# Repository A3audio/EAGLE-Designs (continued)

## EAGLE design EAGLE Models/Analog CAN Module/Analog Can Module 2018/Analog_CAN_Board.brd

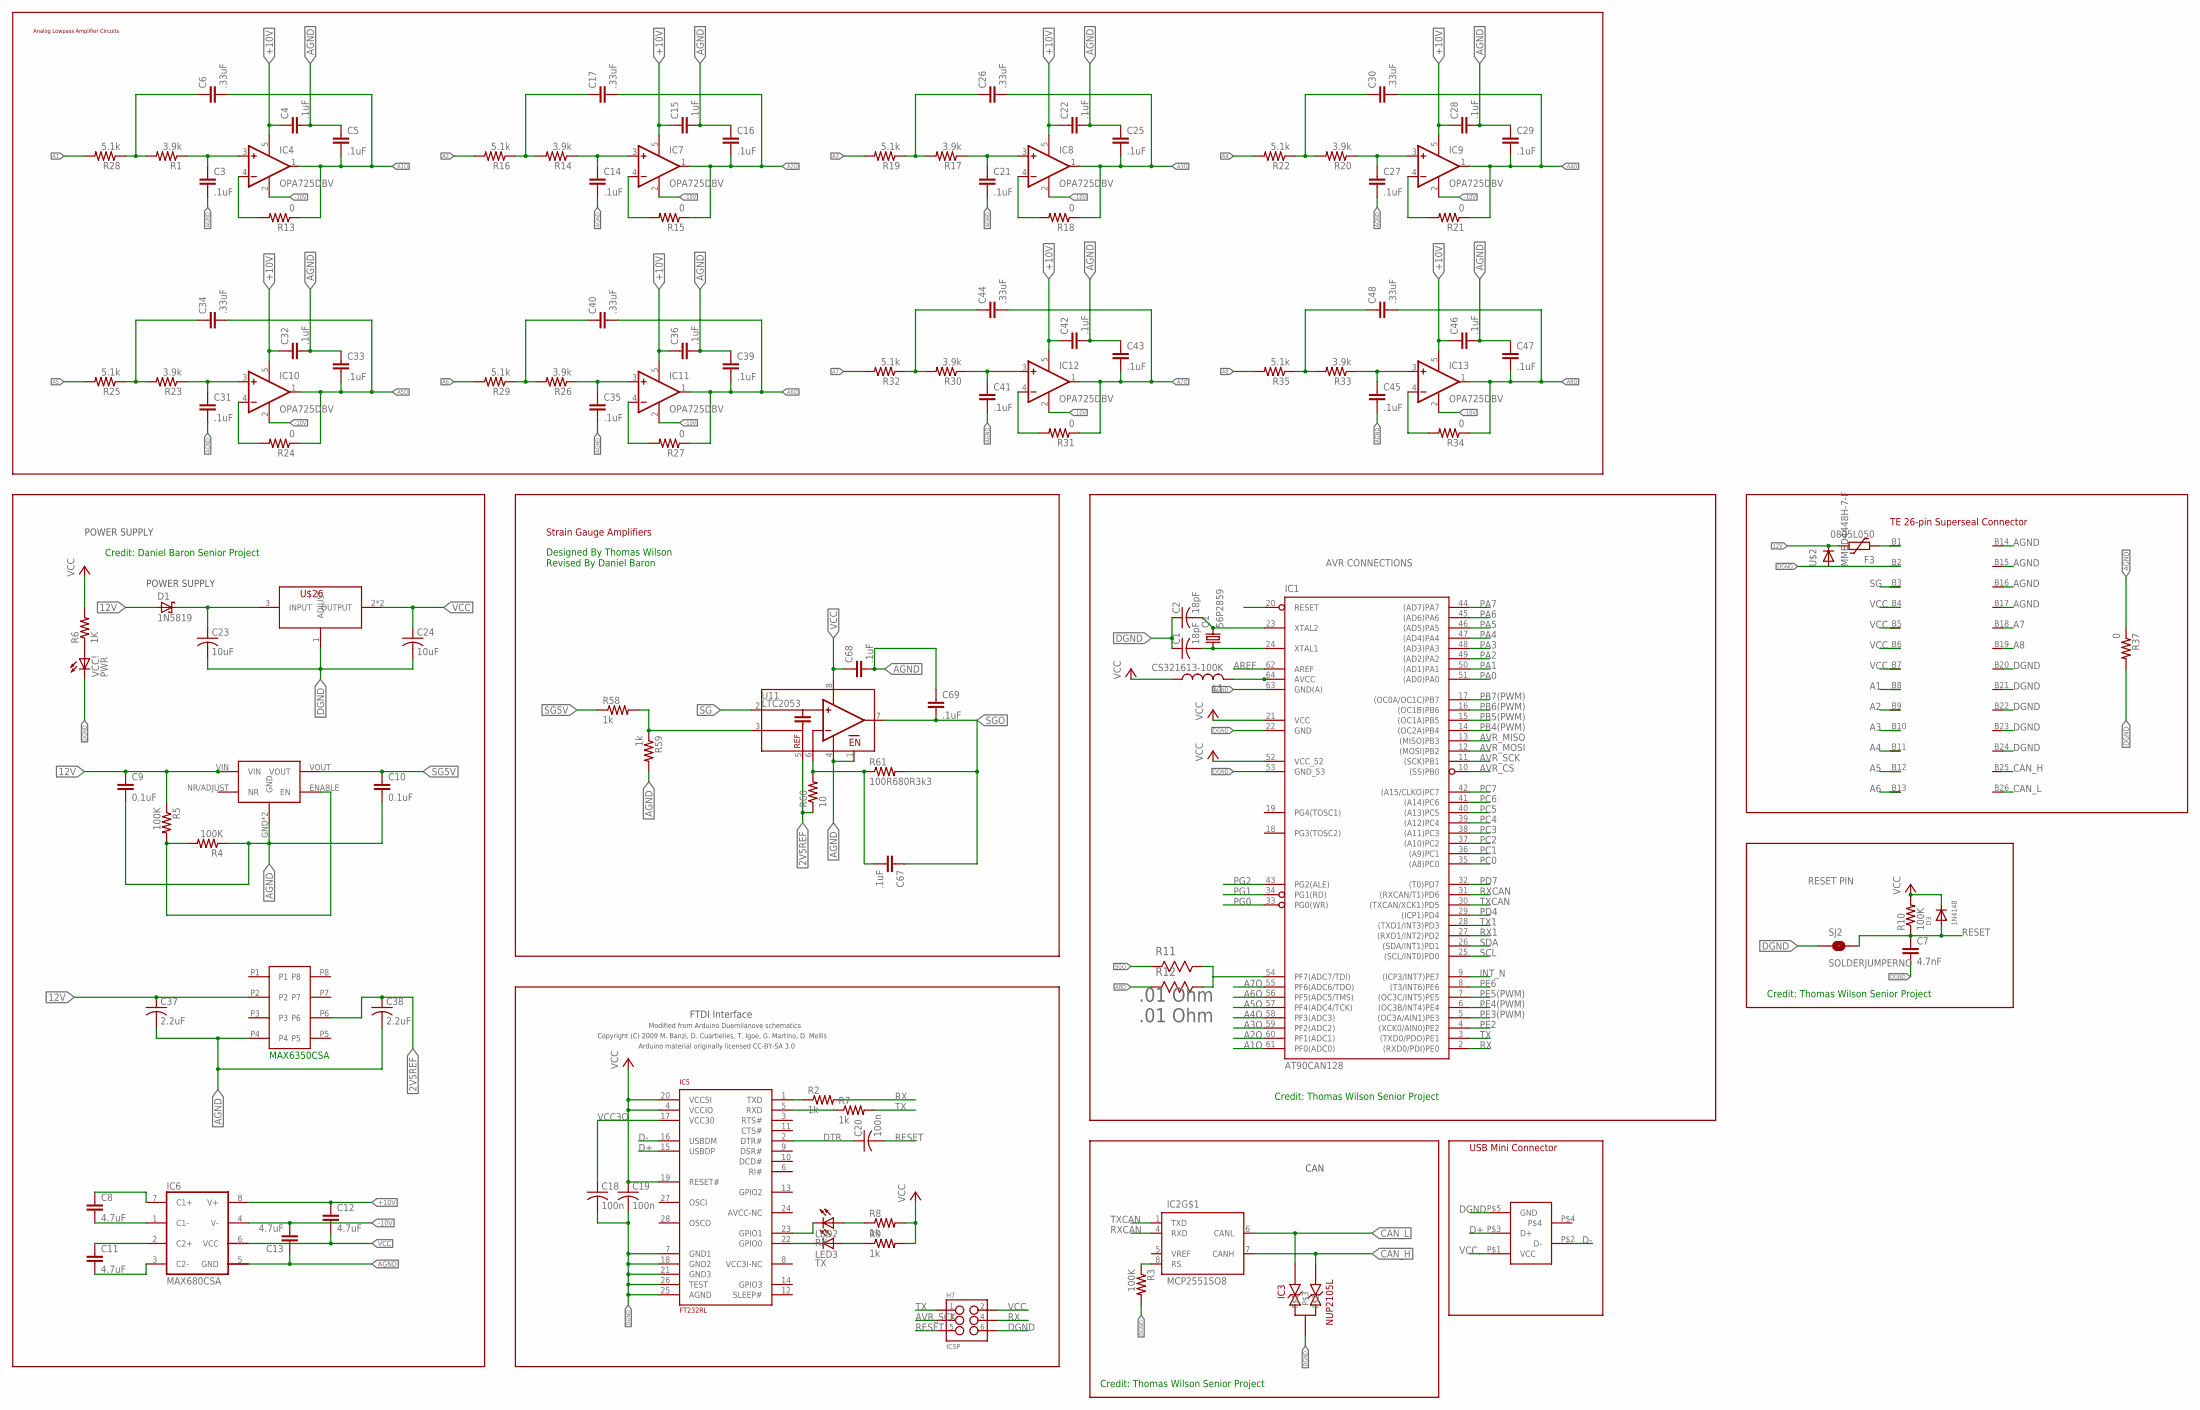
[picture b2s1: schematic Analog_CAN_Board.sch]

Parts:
C1, C2: 18pF; C0805
C3, C4, C5, C14, C15, C16, C21, C22, C25, C27, C28, C29, C31, C32, C33, C35, C36, C39, C41, C42, C43, C45, C46, C47, C67, C68, C69: .1uF; 0603-CAP
C6, C17, C26, C30, C34, C40, C44, C48: .33uF; 0603-CAP
C7: 4.7nF; 0603-CAP
C8, C11, C12, C13: 4.7uF; 0603-CAP
C9, C10: 0.1uF; C0603
C18, C19, C20: 100n; C0805
C23, C24: 10uF; C0603
C37, C38: 2.2uF; C0603
D1: 1N5819; DO41-7.6
D3: 1N4148; SOD-123
F3: 0805L050; 0805L
H7: ICSP; 2X3_SMD_FCI_54202-G30
IC1: AT90CAN128; TQFP64
IC2: MCP2551SO8; SO08
IC3: NUP2105L; SOT-23
IC4, IC7, IC8, IC9, IC10, IC11, IC12, IC13: OPA725DBV; SOT23-5
IC5: FT232RL; SSOP28
IC6: MAX680CSA; SO08
L1: CS321613-100K; L3216C
LED2: RX; CHIPLED_0805
LED3: TX; CHIPLED_0805
Q1: 56P2859; HC49UP
R1, R14, R17, R20, R23, R26, R30, R33: 3.9k; 0603-RES
R2, R7, R8, R9: 1k; R0805
R3, R10: 100K; R0805
R4, R5: 100K; M0805
R6: 1K; R0805
R11, R12: .01 Ohm; RESC1608X60N
R13, R15, R18, R21, R24, R27, R31, R34, R37: 0; 0603-RES
R16, R19, R22, R25, R28, R29, R32, R35: 5.1k; 0603-RES
R58, R59: 1k; 0603-RES
R60: 10; 0603-RES
R61: 100R680R3k3; 0603-RES
SJ2: SOLDERJUMPERNO; SJ_2S-NO
U11: LTC2053; MSOP8
U$1: 1734753-1_MINIUSB_CON
U$2: MMBD4448H-7-F; SOT23-3
U$3: SUPERSEAL1.0_26POS
U$5: REG-104GA-5; REG104GA-5
U$10V2V5: MAX6350CSA; 8-SOIC
U$26: NCP1117; SOT-223-4
VCC!: PWR; CHIPLED_0805

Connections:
2V5REF: C38.1, R60.1, U11.5 (REF), U$10V2V5.P6
5V_REG_IN: C23.1, D1.C, U$26.3 (INPUT)
12V: C9.1, C37.1, D1.A, F3.1, R5.1, U$2.3 (C), U$5.VIN, U$10V2V5.P2
+10V: C4.1, C12.1, C15.1, C22.1, C28.1, C32.1, C36.1, C42.1, C46.1, IC4.5 (V+), IC6.8 (V+), IC7.5 (V+), IC8.5 (V+), IC9.5 (V+), IC10.5 (V+), IC11.5 (V+), IC12.5 (V+), IC13.5 (V+)
-10V: C13.2, IC4.2 (V-), IC6.4 (V-), IC7.2 (V-), IC8.2 (V-), IC9.2 (V-), IC10.2 (V-), IC11.2 (V-), IC12.2 (V-), IC13.2 (V-)
A1: R28.2, U$3.B8
A1O: C5.2, C6.2, IC1.61 (PF0(ADC0)), IC4.1 (OUT), R13.1
A2: R16.2, U$3.B9
A2O: C16.2, C17.2, IC1.60 (PF1(ADC1)), IC7.1 (OUT), R15.1
A3: R19.2, U$3.B10
A3O: C25.2, C26.2, IC1.59 (PF2(ADC2)), IC8.1 (OUT), R18.1
A4: R22.2, U$3.B11
A4O: C29.2, C30.2, IC1.58 (PF3(ADC3)), IC9.1 (OUT), R21.1
A5: R25.2, U$3.B12
A5O: C33.2, C34.2, IC1.57 (PF4(ADC4/TCK)), IC10.1 (OUT), R24.1
A6: R29.2, U$3.B13
A6O: C39.2, C40.2, IC1.56 (PF5(ADC5/TMS)), IC11.1 (OUT), R27.1
A7: R32.2, U$3.B18
A7O: C43.2, C44.2, IC1.55 (PF6(ADC6/TDO)), IC12.1 (OUT), R31.1
A8: R35.2, U$3.B19
A8O: C47.2, C48.2, IC13.1 (OUT), R12.2, R34.1
AGND: C3.2, C4.2, C5.1, C9.2, C10.2, C13.1, C14.2, C15.2, C16.1, C21.2, C22.2, C25.1, C27.2, C28.2, C29.1, C31.2, C32.2, C33.1, C35.2, C36.2, C37.2, C38.2, C39.1, C41.2, C42.2, C43.1, C45.2, C46.2, C47.1, C68.2, C69.1, IC1.63 (GND(A)), IC2.2 (GND), IC6.5 (GND), R4.1, R37.1, R59.2, U11.1 (EN), U11.4 (V-), U$3.B14, U$3.B15, U$3.B16, U$3.B17, U$5.GND, U$5.HEATGND (GND), U$10V2V5.P4
AREF: IC1.62 (AREF)
AVR_CS: IC1.10 ((SS)PB0)
AVR_MISO: IC1.13 ((MISO)PB3)
AVR_MOSI: IC1.12 ((MOSI)PB2)
AVR_SCK: H7.3, IC1.11 ((SCK)PB1)
CAN_H: IC2.7 (CANH), IC3.2, U$3.B25
CAN_L: IC2.6 (CANL), IC3.1, U$3.B26
D+: IC5.15 (USBDP), U$1.P$3 (D+)
D-: IC5.16 (USBDM), U$1.P$2 (D-)
DGND: C1.1, C2.1, C7.2, C18.2, C19.2, C23.2, C24.2, H7.6, IC1.22 (GND), IC1.53 (GND_53), IC3.3, IC5.7 (GND1), IC5.18 (GND2), IC5.21 (GND3), IC5.25 (AGND), IC5.26 (TEST), R3.2, R37.2, SJ2.1, U$1.P$5 (GND), U$2.1 (A), U$3.B2, U$3.B20, U$3.B21, U$3.B22, U$3.B23, U$3.B24, U$26.1 (ADJUST), VCC!.C
DTR: C20.1, IC5.2 (DTR#)
INT_N: IC1.9 ((ICP3/INT7)PE7)
M8RXD: IC5.1 (TXD), R2.1
M8TXD: IC5.5 (RXD), R7.1
unnamed: F3.2, U$3.B1
unnamed: R4.2, R5.2, U$5.ENABLE (EN)
unnamed: C6.1, R1.2, R28.1
unnamed: IC2.8 (RS), R3.1
unnamed: R6.1, VCC!.A
unnamed: C1.2, IC1.24 (XTAL1), Q1.1
unnamed: C3.1, IC4.3 (+IN), R1.1
unnamed: IC1.54 (PF7(ADC7/TDI)), R11.1, R12.1
unnamed: IC4.4 (-IN), R13.2
unnamed: C8.1, IC6.7 (C1+)
unnamed: C11.1, IC6.2 (C2+)
unnamed: IC1.64 (AVCC), L1.2
unnamed: C8.2, IC6.1 (C1-)
unnamed: C11.2, IC6.3 (C2-)
unnamed: C14.1, IC7.3 (+IN), R14.1
unnamed: IC7.4 (-IN), R15.2
unnamed: C17.1, R14.2, R16.1
unnamed: R58.2, R59.1, U11.3 (+IN)
unnamed: C67.2, R60.2, R61.1, U11.6 (RG)
unnamed: C21.1, IC8.3 (+IN), R17.1
unnamed: IC8.4 (-IN), R18.2
unnamed: IC5.23 (GPIO1), LED2.C
unnamed: C26.1, R17.2, R19.1
unnamed: IC5.22 (GPIO0), LED3.C
unnamed: LED2.A, R8.1
unnamed: LED3.A, R9.1
unnamed: C27.1, IC9.3 (+IN), R20.1
unnamed: IC9.4 (-IN), R21.2
unnamed: C30.1, R20.2, R22.1
unnamed: C31.1, IC10.3 (+IN), R23.1
unnamed: IC10.4 (-IN), R24.2
unnamed: C34.1, R23.2, R25.1
unnamed: C35.1, IC11.3 (+IN), R26.1
unnamed: IC11.4 (-IN), R27.2
unnamed: C40.1, R26.2, R29.1
unnamed: C41.1, IC12.3 (+IN), R30.1
unnamed: IC12.4 (-IN), R31.2
unnamed: C44.1, R30.2, R32.1
unnamed: C45.1, IC13.3 (+IN), R33.1
unnamed: IC13.4 (-IN), R34.2
unnamed: C48.1, R33.2, R35.1
PA0: IC1.51 ((AD0)PA0)
PA1: IC1.50 ((AD1)PA1)
PA2: IC1.49 ((AD2)PA2)
PA3: IC1.48 ((AD3)PA3)
PA4: IC1.47 ((AD4)PA4)
PA5: IC1.46 ((AD5)PA5)
PA6: IC1.45 ((AD6)PA6)
PA7: IC1.44 ((AD7)PA7)
PB4(PWM): IC1.14 ((OC2A)PB4)
PB5(PWM): IC1.15 ((OC1A)PB5)
PB6(PWM): IC1.16 ((OC1B)PB6)
PB7(PWM): IC1.17 ((OC0A/OC1C)PB7)
PC0: IC1.35 ((A8)PC0)
PC1: IC1.36 ((A9)PC1)
PC2: IC1.37 ((A10)PC2)
PC3: IC1.38 ((A11)PC3)
PC4: IC1.39 ((A12)PC4)
PC5: IC1.40 ((A13)PC5)
PC6: IC1.41 ((A14)PC6)
PC7: IC1.42 ((A15/CLKO)PC7)
PD4: IC1.29 ((ICP1)PD4)
PD7: IC1.32 ((T0)PD7)
PE2: IC1.4 ((XCK0/AIN0)PE2)
PE3(PWM): IC1.5 ((OC3A/AIN1)PE3)
PE4(PWM): IC1.6 ((OC3B/INT4)PE4)
PE5(PWM): IC1.7 ((OC3C/INT5)PE5)
PE6: IC1.8 ((T3/INT6)PE6)
PG0: IC1.33 (PG0(WR))
PG1: IC1.34 (PG1(RD))
PG2: IC1.43 (PG2(ALE))
RESET: C7.1, C20.2, D3.A, H7.5, IC1.20 (RESET), R10.1, SJ2.2
RX: H7.4, IC1.2 ((RXD0/PDI)PE0), R2.2
RX1: IC1.27 ((RXD1/INT2)PD2)
RXCAN: IC1.31 ((RXCAN/T1)PD6), IC2.4 (RXD)
SCL: IC1.25 ((SCL/INT0)PD0)
SDA: IC1.26 ((SDA/INT1)PD1)
SG: U11.2 (-IN), U$3.B3
SG5V: C10.1, R58.1, U$5.VOUT
SGO: C67.1, C69.2, R11.2, R61.2, U11.7 (OUT)
TX: H7.1, IC1.3 ((TXD0/PDO)PE1), R7.2
TX1: IC1.28 ((TXD1/INT3)PD3)
TXCAN: IC1.30 ((TXCAN/XCK1)PD5), IC2.1 (TXD)
VCC: C12.2, C19.1, C24.1, C68.1, D3.C, H7.2, IC1.21 (VCC), IC1.52 (VCC_52), IC2.3 (VCC), IC5.4 (VCCIO), IC5.19 (RESET#), IC5.20 (VCC5I), IC6.6 (VCC), L1.1, R6.2, R8.2, R9.2, R10.2, U11.8 (V+), U$1.P$1 (VCC), U$3.B4, U$3.B5, U$3.B6, U$3.B7, U$26.2 (OUTPUT), U$26.4 (OUTPUT)
VCC3O: C18.1, IC5.17 (VCC30)
XTAL1: C2.2, IC1.23 (XTAL2), Q1.2

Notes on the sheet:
CAN
AVR CONNECTIONS
Credit: Thomas Wilson Senior Project
Strain Gauge Amplifiers
POWER SUPPLY
FTDI Interface
Modified from Arduino Duemilanove schematics
Copyright (C) 2009 M. Banzi, D. Cuartielles, T. Igoe, G. Martino, D. Mellis
Arduino material originally licensed CC-BY-SA 3.0
MAX6350CSA
Designed By Thomas Wilson Revised By Daniel Baron
TE 26-pin Superseal Connector
RESET PIN
USB Mini Connector
Credit: Daniel Baron Senior Project
Analog Lowpass Amplifier Circuits

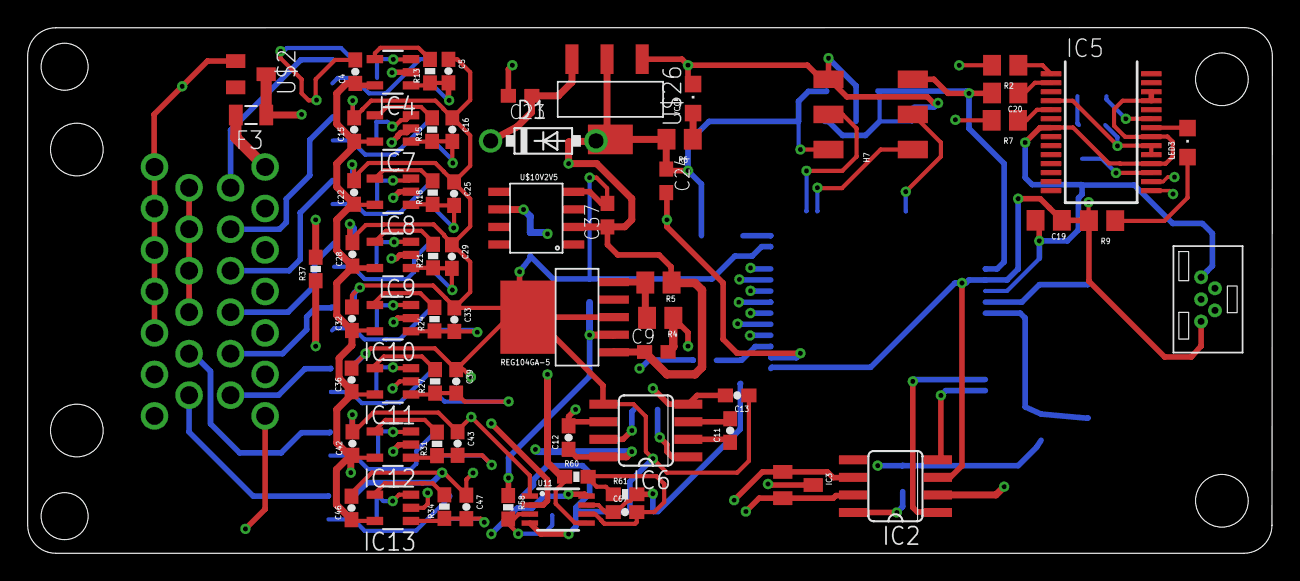
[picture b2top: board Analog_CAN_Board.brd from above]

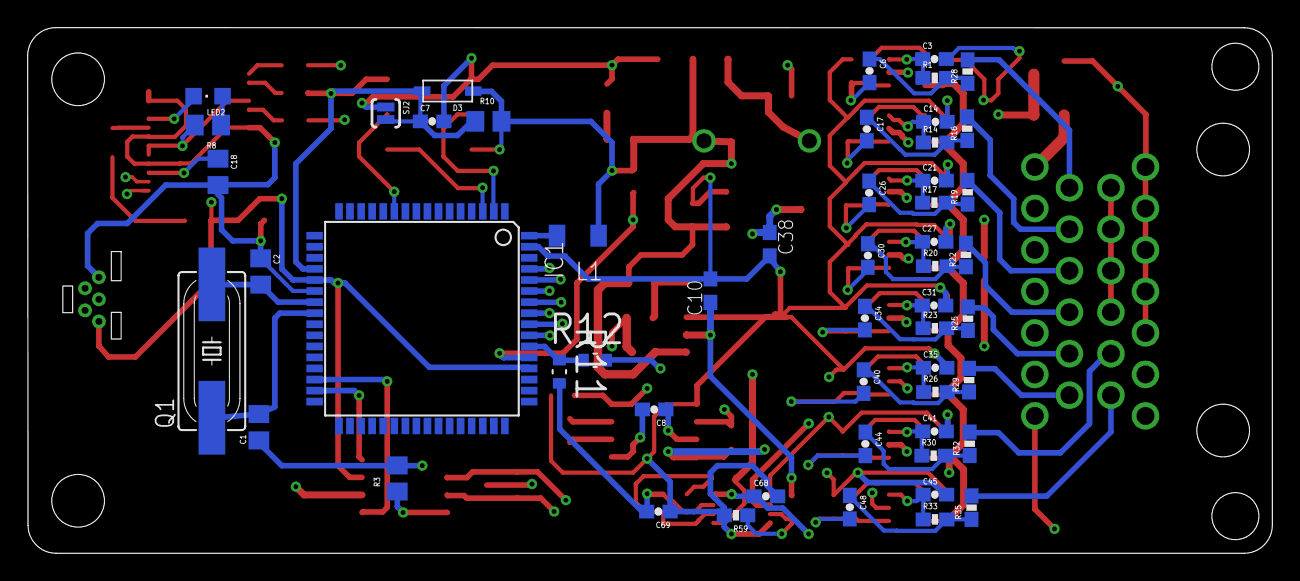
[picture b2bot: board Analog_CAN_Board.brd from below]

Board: 4 copper layers, 90.0 x 38.0 mm, 121 parts (53 on the bottom side), 83 nets.

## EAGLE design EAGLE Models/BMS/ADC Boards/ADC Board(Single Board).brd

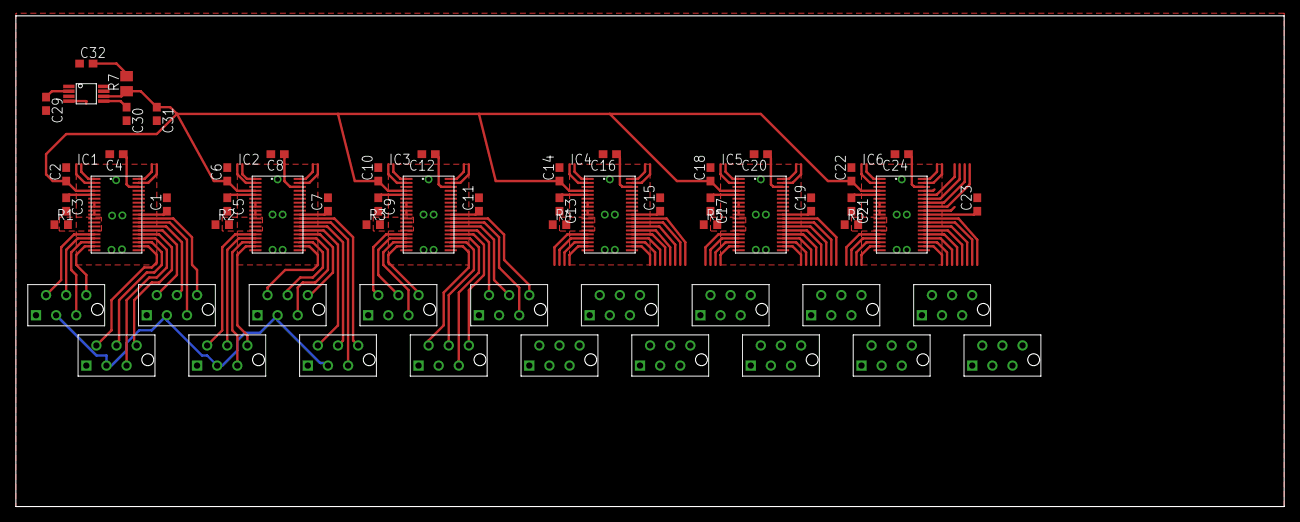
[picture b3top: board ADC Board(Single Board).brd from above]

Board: 2 copper layers, 160.0 x 61.9 mm, 60 parts (0 on the bottom side), 92 nets.

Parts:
C1, C3, C4, C5, C7, C8, C9, C11, C12, C13, C15, C16, C17, C19, C20, C21, C23, C24, C29, C30, C31: 1uF; C0603
C2, C6, C10, C14, C18, C22: 10uF; C0603
C32: 22uF; C0603
IC1, IC2, IC3, IC4, IC5, IC6: ADS7956; TSSOP-38
R1, R2, R3, R4, R5, R6: 10k; R0603
R7: 1; M0805
U$1: REF5025; TSSOP-8(TI)
X1, X2, X3, X4, X5, X6, X7, X8, X9, X10, X11, X12, X13, X14, X15, X16, X17, X18: 6_PIN_CONNTE_IDC; 2178710_IDC

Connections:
2.5VREF: C2.1, C6.1, C10.1, C14.1, C18.1, C22.1, C31.1, IC1.P$4, IC2.P$4, IC3.P$4, IC4.P$4, IC5.P$4, IC6.P$4, R7.1, U$1.P$6
AIN0: IC1.P$28, X1.P$3
AIN1: IC1.P$27, X1.P$4
AIN2: IC1.P$26, X1.P$5
AIN3: IC1.P$25, X1.P$6
AIN4: IC1.P$24, X2.P$3
AIN5: IC1.P$23, X2.P$4
AIN6: IC1.P$22, X2.P$5
AIN7: IC1.P$21, X2.P$6
AIN8: IC1.P$18, X3.P$3
AIN9: IC1.P$17, X3.P$4
AIN10: IC1.P$16, X3.P$5
AIN11: IC1.P$15, X3.P$6
AIN12: IC2.P$28, X10.P$3
AIN13: IC2.P$27, X10.P$4
AIN14: IC2.P$26, X10.P$5
AIN15: IC2.P$25, X10.P$6
AIN16: IC2.P$24, X11.P$3
AIN17: IC2.P$23, X11.P$4
AIN18: IC2.P$22, X11.P$5
AIN19: IC2.P$21, X11.P$6
AIN20: IC2.P$18, X12.P$3
AIN21: IC2.P$17, X12.P$4
AIN22: IC2.P$16, X12.P$5
AIN23: IC2.P$15, X12.P$6
AIN24: IC3.P$28, X4.P$3
AIN25: IC3.P$27, X4.P$4
AIN26: IC3.P$26, X4.P$5
AIN27: IC3.P$25, X4.P$6
AIN28: IC3.P$24, X5.P$3
AIN29: IC3.P$23, X5.P$4
AIN30: IC3.P$22, X5.P$5
AIN31: IC3.P$21, X5.P$6
AIN32: IC3.P$18, X6.P$3
AIN33: IC3.P$17, X6.P$4
AIN34: IC3.P$16, X6.P$5
AIN35: IC3.P$15, X6.P$6
AIN36: IC5.P$28, X13.P$3
AIN37: IC5.P$27, X13.P$4
AIN38: IC5.P$26, X13.P$5
AIN39: IC5.P$25, X13.P$6
AIN40: IC5.P$24, X14.P$3
AIN41: IC5.P$23, X14.P$4
AIN42: IC5.P$22, X14.P$5
AIN43: IC5.P$21, X14.P$6
AIN44: IC5.P$18, X15.P$3
AIN45: IC5.P$17, X15.P$4
AIN46: IC5.P$16, X15.P$5
AIN48: IC4.P$28, X7.P$3
AIN49: IC4.P$27, X7.P$4
AIN50: IC4.P$26, X7.P$5
AIN51: IC4.P$25, X7.P$6
AIN52: IC4.P$24, X8.P$3
AIN53: IC4.P$23, X8.P$4
AIN54: IC4.P$22, X8.P$5
AIN55: IC4.P$21, X8.P$6
AIN56: IC4.P$18, X9.P$3
AIN57: IC4.P$17, X9.P$4
AIN58: IC4.P$16, X9.P$5
AIN59: IC4.P$15, X9.P$6
AIN60: IC6.P$28, X16.P$3
AIN61: IC6.P$27, X16.P$4
AIN62: IC6.P$26, X16.P$5
AIN63: IC6.P$25, X16.P$6
AIN64: IC6.P$24, X17.P$3
AIN65: IC6.P$23, X17.P$4
AIN66: IC6.P$22, X17.P$5
AIN67: IC6.P$21, X17.P$6
AIN68: IC6.P$18, X18.P$3
AIN69: IC6.P$17, X18.P$4
AIN70: IC6.P$16, X18.P$5
AIN71: IC6.P$15, X18.P$6
A_INPUT0: IC1.P$7, IC1.P$8
A_INPUT1: IC2.P$7, IC2.P$8
A_INPUT2: IC3.P$7, IC3.P$8
A_INPUT3: IC5.P$7, IC5.P$8
A_INPUT4: IC4.P$7, IC4.P$8
A_INPUT5: IC6.P$7, IC6.P$8
GND: C1.2, C2.2, C3.2, C4.2, C5.2, C6.2, C7.2, C8.2, C9.2, C10.2, C11.2, C12.2, C13.2, C14.2, C15.2, C16.2, C17.2, C18.2, C19.2, C20.2, C21.2, C22.2, C23.2, C24.2, C29.2, C30.2, C31.2, C32.1, IC1.P$3, IC1.P$6, IC1.P$9, IC1.P$10, IC1.P$19, IC1.P$20, IC1.P$30, IC1.P$35, IC2.P$3, IC2.P$6, IC2.P$9, IC2.P$10, IC2.P$19, IC2.P$20, IC2.P$30, IC2.P$35, IC3.P$3, IC3.P$6, IC3.P$9, IC3.P$10, IC3.P$19, IC3.P$20, IC3.P$30, IC3.P$35, IC4.P$3, IC4.P$6, IC4.P$9, IC4.P$10, IC4.P$19, IC4.P$20, IC4.P$30, IC4.P$35, IC5.P$3, IC5.P$6, IC5.P$9, IC5.P$10, IC5.P$19, IC5.P$20, IC5.P$30, IC5.P$35, IC6.P$3, IC6.P$6, IC6.P$9, IC6.P$10, IC6.P$19, IC6.P$20, IC6.P$30, IC6.P$35, R1.1, R2.1, R3.1, R4.1, R5.1, R6.1, U$1.P$4, X1.P$1, X2.P$1, X3.P$1, X4.P$1, X5.P$1, X6.P$1, X7.P$1, X8.P$1, X9.P$1, X10.P$1, X11.P$1, X12.P$1, X13.P$1, X14.P$1, X15.P$1, X16.P$1, X17.P$1, X18.P$1
unnamed: C32.2, R7.2
NC: IC1.P$11, IC1.P$12, IC1.P$13, IC1.P$14, R1.2
NC1: IC2.P$11, IC2.P$12, IC2.P$13, IC2.P$14, R2.2
NC2: IC3.P$11, IC3.P$12, IC3.P$13, IC3.P$14, R3.2
NC3: IC4.P$11, IC4.P$12, IC4.P$13, IC4.P$14, R4.2
NC4: IC5.P$11, IC5.P$12, IC5.P$13, IC5.P$14, R5.2
NC5: IC6.P$11, IC6.P$12, IC6.P$13, IC6.P$14, R6.2
SCLK: IC1.P$32, IC2.P$32, IC3.P$32, IC4.P$32, IC5.P$32, IC6.P$32
SDI: IC1.P$33, IC2.P$33, IC3.P$33, IC4.P$33, IC5.P$33, IC6.P$33
SDO: IC1.P$34, IC2.P$34, IC3.P$34, IC4.P$34, IC5.P$34, IC6.P$34
TRIM: C30.1, U$1.P$5
VA: C1.1, C3.1, C5.1, C7.1, C9.1, C11.1, C13.1, C15.1, C17.1, C19.1, C21.1, C23.1, IC1.P$5, IC1.P$29, IC2.P$5, IC2.P$29, IC3.P$5, IC3.P$29, IC4.P$5, IC4.P$29, IC5.P$5, IC5.P$29, IC6.P$5, IC6.P$29, X1.P$2, X2.P$2, X3.P$2, X4.P$2, X5.P$2, X6.P$2, X7.P$2, X8.P$2, X9.P$2, X10.P$2, X11.P$2, X12.P$2, X13.P$2, X14.P$2, X15.P$2, X16.P$2, X17.P$2, X18.P$2
VCC: C4.1, C8.1, C12.1, C16.1, C20.1, C24.1, C29.1, IC1.P$36, IC2.P$36, IC3.P$36, IC4.P$36, IC5.P$36, IC6.P$36, U$1.P$2

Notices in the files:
parts and their libraries:
SparkFun-Passives: Licensing: CC v3.0 Share-Alike You are welcome to use this library for commercial purposes.
